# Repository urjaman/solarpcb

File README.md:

# "Solar" PCB
--------------

Shared at oshpark:
<https://oshpark.com/shared_projects/fC9XhvWo>

This is a tiny PCB facilitating (atleast) two different circuits
that implement charging of a *protected* li-ion cell + night-light
functionality from a solar panel (usual suspect is one of those
6V 1W ones).

## Simpler ciruit - one N-fet ##
- Install the B- to S- diode
- Install the N-fet on the bottom (nearer to B+/B-) position
- bridge B+ to S+ (no diode, just a wire)
- bridge the S- to FET resistor position
- bridge the SMD solder jumper from the LOAD- to the 1st FET output

This circuit will activate the nightlight when Vpanel < (Vbattery - Vth),
that is you need almost the full battery voltage to turn off the load.

Effective schematic:

    S+ ---------------- B+ & L+
    
               /------- L-
        /----| Q
        |      |
    S- -*-|<---*------- B-

## Two-fet circuit ##
- Install the S+ to B+ diode
- install both N-fets
- install the pull-up resistor from B+ - eg. 470k
- bridge the S+ to FET resistor position
- bridge B- to S-

This ciruit will activate the nightlight when Vpanel < Vth, that is
it disables the load much earlier, at the cost of a few microamps
through the pull-up resistor during the off-time.

Effective schematic:

    S+ -*->|----*------ B+ & L+
        |       |
        |       R
        |       |    /- L-
        |    /--*--| Q
        \--| Q       |
             |       |
    S- ------*-------*- B- 

## Things and stuff ##

The PCB will facilitate either TO-92-style transistors where
the gate/base is the middle pin or SOT-23 with the GSD
pin order, eg. AO3400, IRLML2502, IRLML6344. 

For resistors there is a through-hole pattern and a
hand-soldering friendly 0805 SMD pattern (that you can
likely put a size up or down into too).

For diodes it will take basic through-hole ones (1N5817 or similar)
and SMD diodes from SMB to SOD-323 (and SMA and SOD-123 on the way).

I prefer FETs for this circuit (primarily because they need almost
no current to switch) but it should be workable with BJTs too,
just use a resistor instead of the link for the control line.

You could also play with resistors on both positions to adjust 
the light thresholds, etc... just look at the schematic
and have fun :P.

Another funky idea: put a BJT on the second transistor position
and set it up as a slightly more constant current source for
your LEDs...

For funsies the entire schematic ASCIIfied:

    S+ -*->|----*--------- B+ & L+
        |       |
        R       R  /-J-*-- L-
        |       |  |   |
        |    /--*--*-| Q
        *--| Q         |
        |    |         |
        R    |         |
        |    |         |
    S- -*-|<-*---------*-- B-

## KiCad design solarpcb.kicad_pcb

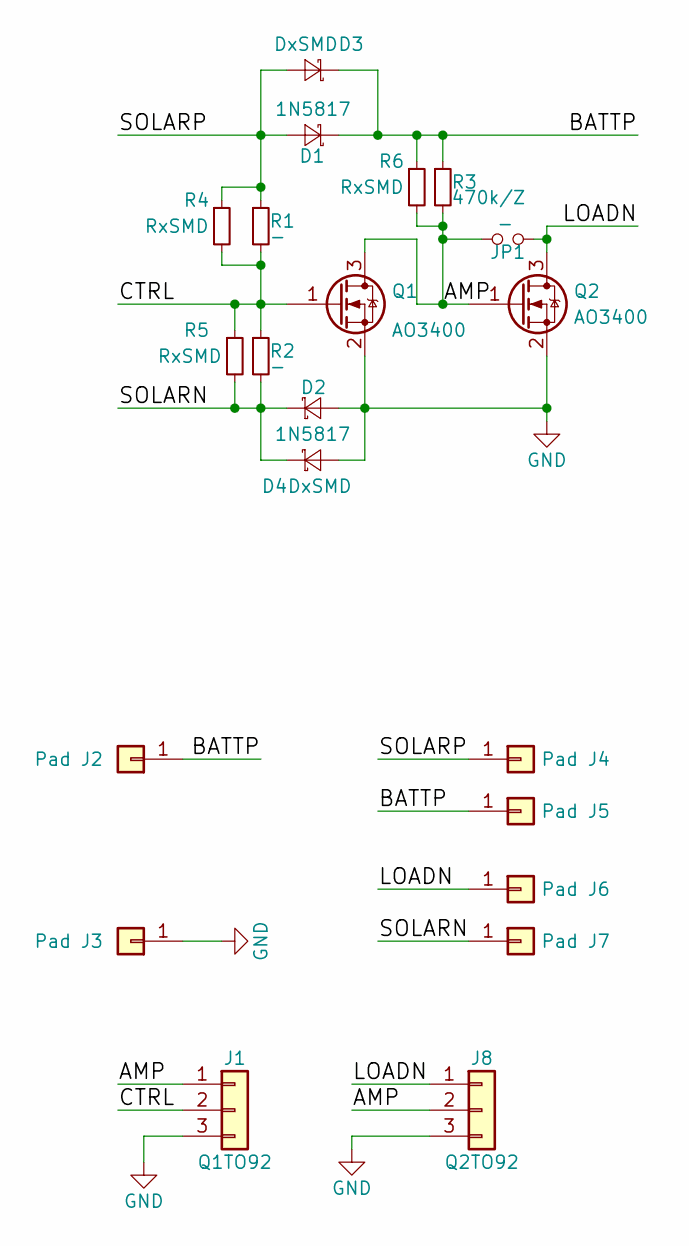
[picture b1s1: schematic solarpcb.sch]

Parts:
D1, D2: 1N5817; D_DO-41_SOD81_P7.62mm_Horizontal
D3, D4: DxSMD; D_SMA-SMB_Universal_Handsoldering
J1: Q1TO92; Pin_Header_Straight_1x03_Pitch2.00mm
J2, J3, J4, J5, J6, J7: Pad; Pin_Header_Straight_1x01_Pitch2.54mm
J8: Q2TO92; Pin_Header_Straight_1x03_Pitch2.00mm
JP1: -; R_0603_HandSoldering
Q1, Q2: AO3400; SOT-23_Handsoldering
R1, R2: -; R_Axial_DIN0207_L6.3mm_D2.5mm_P7.62mm_Horizontal
R3: 470k/Z; R_Axial_DIN0207_L6.3mm_D2.5mm_P7.62mm_Horizontal
R4, R5, R6: RxSMD; R_0805_HandSoldering

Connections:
/AMP: J1.1, J8.2, JP1.2, Q1.3 (D), Q2.1 (G), R3.2, R6.2
/BATTP: D1.1 (K), D3.1 (K), J2.1, J5.1, R3.1, R6.1
/CTRL: J1.2, Q1.1 (G), R1.2, R2.1, R4.2, R5.1
/LOADN: J6.1, J8.1, JP1.1, Q2.3 (D)
/SOLARN: D2.1 (K), D4.1 (K), J7.1, R2.2, R5.2
/SOLARP: D1.2 (A), D3.2 (A), J4.1, R1.1, R4.1
GND: D2.2 (A), D4.2 (A), J1.3, J3.1, J8.3, Q1.2 (S), Q2.2 (S)

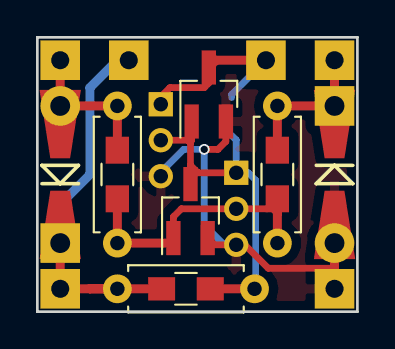
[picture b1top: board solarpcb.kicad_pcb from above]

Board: 2 copper layers, 17.8 x 15.2 mm, 21 parts (1 on the bottom side), 7 nets.

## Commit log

2018-07-03 initial stuff sent to oshpark
2018-07-08 Add explanatory readme
2018-07-08 Add some artistic schematic representations into the readme
2018-07-08 fixing that...
2018-07-08 fixing it v2
2018-07-08 put the link in?
2018-07-08 Add a license
